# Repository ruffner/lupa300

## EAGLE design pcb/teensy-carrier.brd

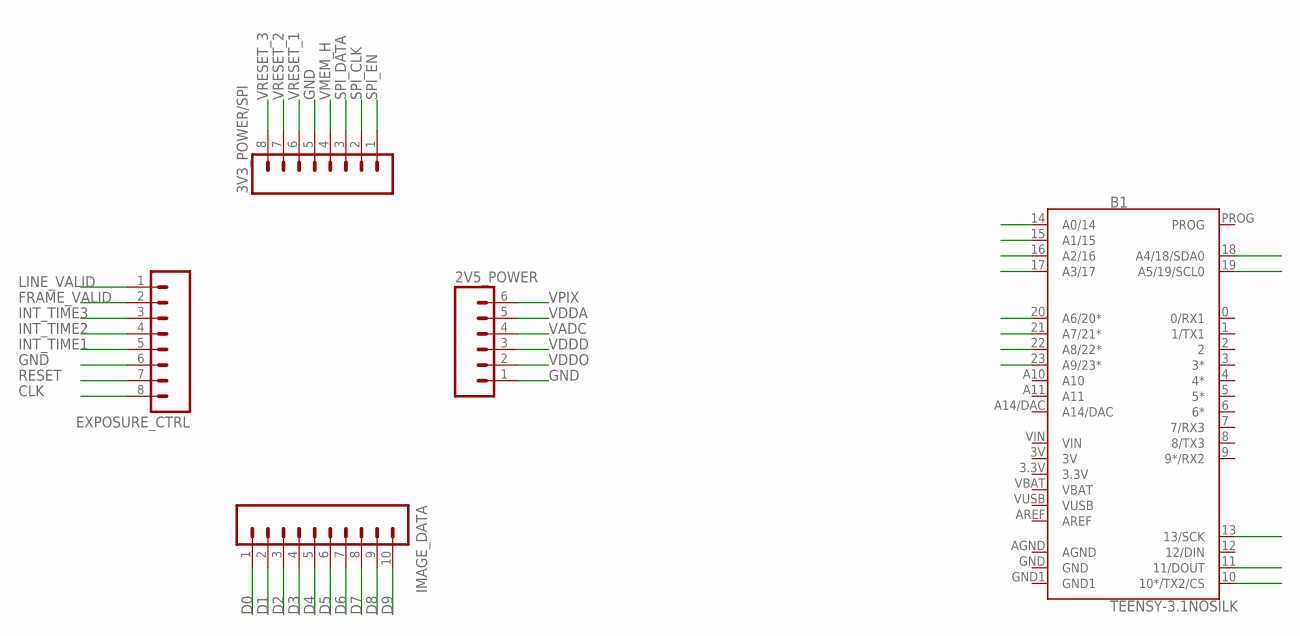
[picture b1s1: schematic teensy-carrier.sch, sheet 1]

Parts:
2V5_POWER: M06SILK_FEMALE_PTH; 1X06
3V3_POWER/SPI: M08; 1X08_ROUND
B1: TEENSY-3.1NOSILK; TEENSY-3.1_NOSILK
EXPOSURE_CTRL: M08; 1X08_ROUND
IMAGE_DATA: M10SILK_FEMALE_PTH; 1X10

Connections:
3.3V: B1.3.3V
3V: B1.3V
AGND: B1.AGND
CLK: EXPOSURE_CTRL.8
D0: B1.23 (A9/23*), IMAGE_DATA.1
D1: B1.22 (A8/22*), IMAGE_DATA.2
D2: B1.21 (A7/21*), IMAGE_DATA.3
D3: B1.20 (A6/20*), IMAGE_DATA.4
D4: B1.19 (A5/19/SCL0), IMAGE_DATA.5
D5: B1.18 (A4/18/SDA0), IMAGE_DATA.6
D6: B1.17 (A3/17), IMAGE_DATA.7
D7: B1.16 (A2/16), IMAGE_DATA.8
D8: B1.15 (A1/15), IMAGE_DATA.9
D9: B1.14 (A0/14), IMAGE_DATA.10
FRAME_VALID: EXPOSURE_CTRL.2
GND: 2V5_POWER.1, 3V3_POWER/SPI.5, B1.GND, EXPOSURE_CTRL.6; also elsewhere on the board
GND1: B1.GND1
INT_TIME1: EXPOSURE_CTRL.5
INT_TIME2: EXPOSURE_CTRL.4
INT_TIME3: EXPOSURE_CTRL.3
LINE_VALID: EXPOSURE_CTRL.1
RESET: EXPOSURE_CTRL.7
SPI_CLK: 3V3_POWER/SPI.2, B1.13 (13/SCK)
SPI_DATA: 3V3_POWER/SPI.3, B1.11 (11/DOUT)
SPI_EN: 3V3_POWER/SPI.1, B1.10 (10*/TX2/CS)
VADC: 2V5_POWER.4; also elsewhere on the board
VBAT: B1.VBAT
VDDA: 2V5_POWER.5; also elsewhere on the board
VDDD: 2V5_POWER.3; also elsewhere on the board
VDDO: 2V5_POWER.2; also elsewhere on the board
VIN: B1.VIN; also elsewhere on the board
VMEM_H: 3V3_POWER/SPI.4; also elsewhere on the board
VPIX: 2V5_POWER.6; also elsewhere on the board
VRESET_1: 3V3_POWER/SPI.6; also elsewhere on the board
VRESET_2: 3V3_POWER/SPI.7
VRESET_3: 3V3_POWER/SPI.8
VUSB: B1.VUSB

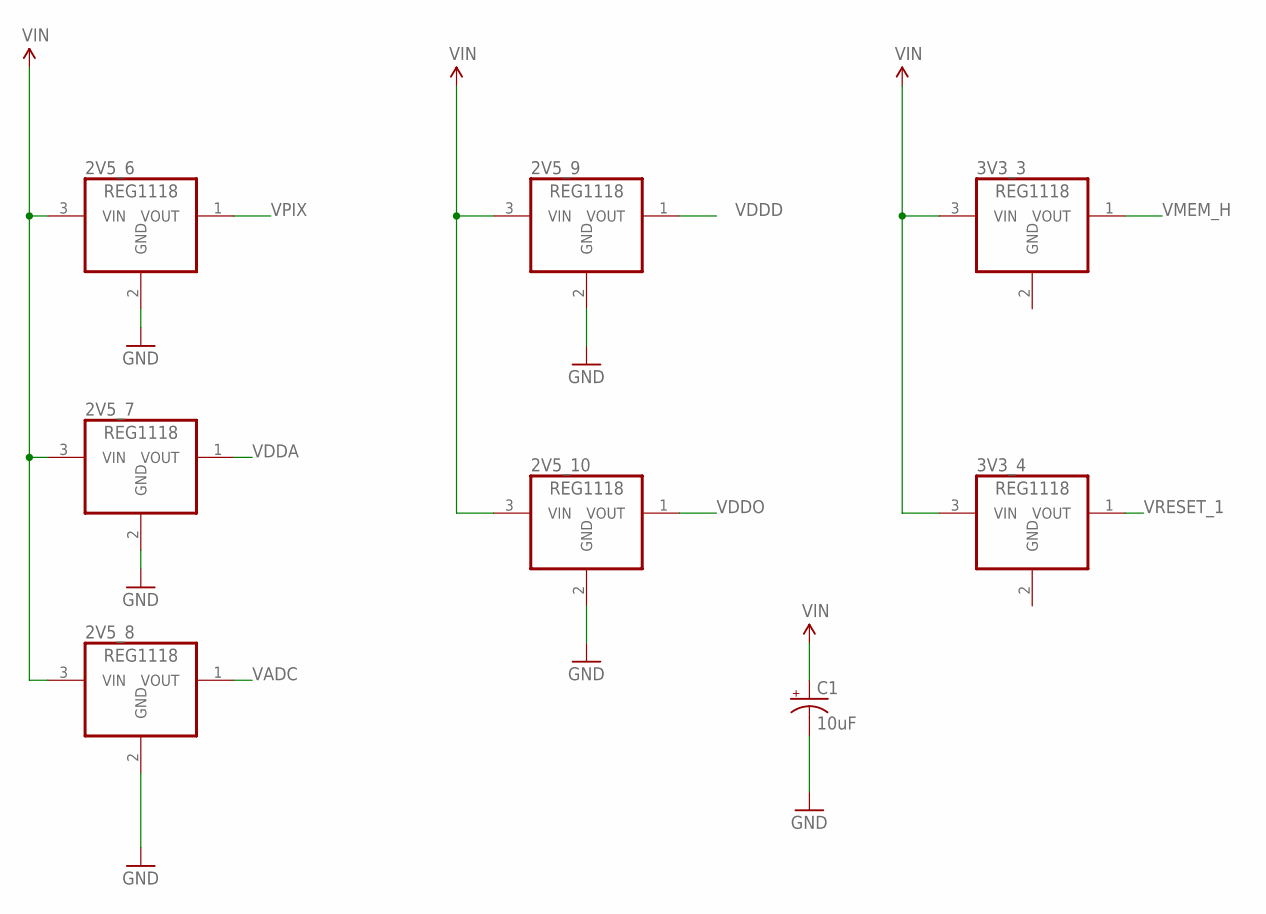
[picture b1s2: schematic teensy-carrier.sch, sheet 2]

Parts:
2V5_6, 2V5_7, 2V5_8, 2V5_9, 2V5_10, 3V3_3, 3V3_4: REG1118; SOT223
C1: 10uF; EIA3216

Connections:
GND: 2V5_6.2 (GND), 2V5_7.2 (GND), 2V5_8.2 (GND), 2V5_9.2 (GND), 2V5_10.2 (GND), 3V3_3.2 (GND), 3V3_4.2 (GND), C1.-; also elsewhere on the board
VADC: 2V5_8.1 (VOUT); also elsewhere on the board
VDDA: 2V5_7.1 (VOUT); also elsewhere on the board
VDDD: 2V5_9.1 (VOUT); also elsewhere on the board
VDDO: 2V5_10.1 (VOUT); also elsewhere on the board
VIN: 2V5_6.3 (VIN), 2V5_7.3 (VIN), 2V5_8.3 (VIN), 2V5_9.3 (VIN), 2V5_10.3 (VIN), 3V3_3.3 (VIN), 3V3_4.3 (VIN), C1.+; also elsewhere on the board
VMEM_H: 3V3_3.1 (VOUT); also elsewhere on the board
VPIX: 2V5_6.1 (VOUT); also elsewhere on the board
VRESET_1: 3V3_4.1 (VOUT); also elsewhere on the board

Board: 2 copper layers, 13 parts (8 on the bottom side), 22 nets, no tracks yet.

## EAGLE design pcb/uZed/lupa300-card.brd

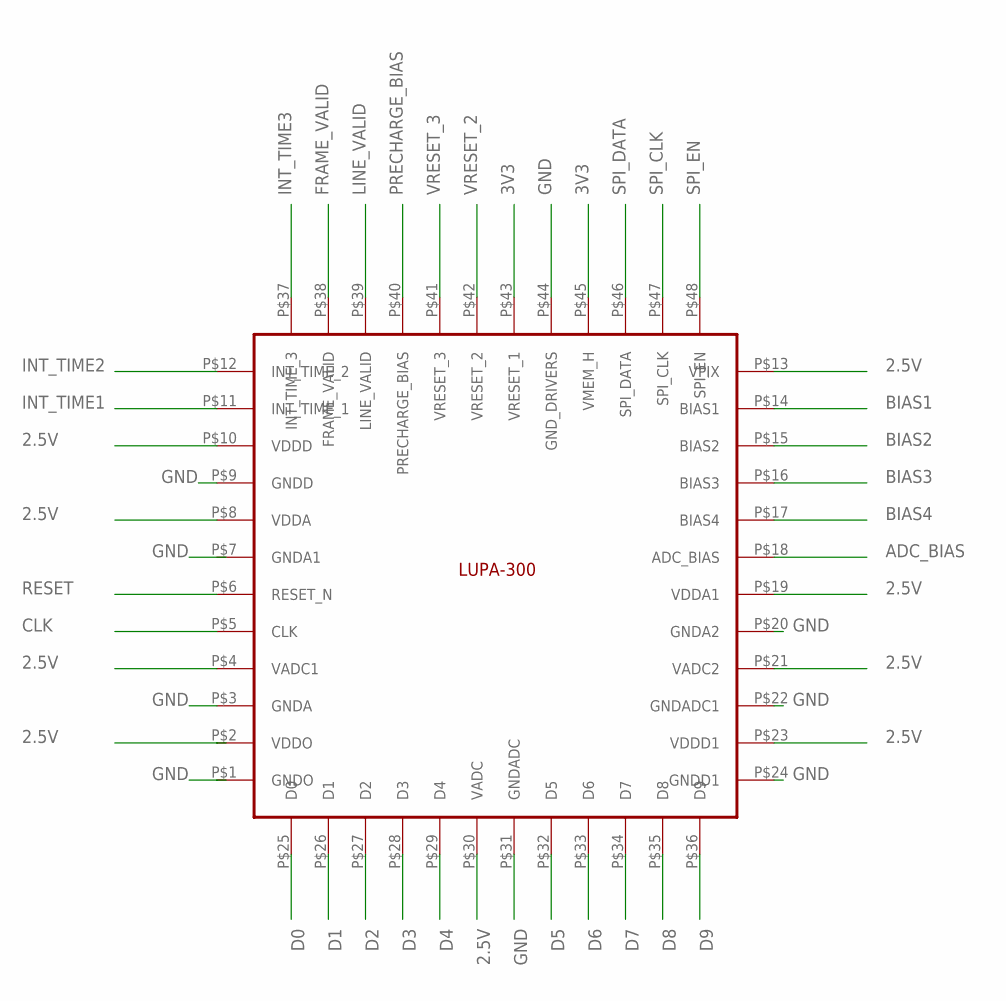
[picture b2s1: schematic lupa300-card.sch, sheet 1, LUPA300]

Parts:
U$1: LUPA300

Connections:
2.5V: U$1.P$2 (VDDO), U$1.P$4 (VADC1), U$1.P$8 (VDDA), U$1.P$10 (VDDD), U$1.P$13 (VPIX), U$1.P$19 (VDDA1), U$1.P$21 (VADC2), U$1.P$23 (VDDD1), U$1.P$30 (VADC); also elsewhere on the board
3V3: U$1.P$43 (VRESET_1), U$1.P$45 (VMEM_H); also elsewhere on the board
ADC_BIAS: U$1.P$18 (ADC_BIAS); also elsewhere on the board
BIAS1: U$1.P$14 (BIAS1); also elsewhere on the board
BIAS2: U$1.P$15 (BIAS2); also elsewhere on the board
BIAS3: U$1.P$16 (BIAS3); also elsewhere on the board
BIAS4: U$1.P$17 (BIAS4); also elsewhere on the board
CLK: U$1.P$5 (CLK); also elsewhere on the board
D0: U$1.P$25 (D0); also elsewhere on the board
D1: U$1.P$26 (D1); also elsewhere on the board
D2: U$1.P$27 (D2); also elsewhere on the board
D3: U$1.P$28 (D3); also elsewhere on the board
D4: U$1.P$29 (D4); also elsewhere on the board
D5: U$1.P$32 (D5); also elsewhere on the board
D6: U$1.P$33 (D6); also elsewhere on the board
D7: U$1.P$34 (D7); also elsewhere on the board
D8: U$1.P$35 (D8); also elsewhere on the board
D9: U$1.P$36 (D9); also elsewhere on the board
FRAME_VALID: U$1.P$38 (FRAME_VALID); also elsewhere on the board
GND: U$1.P$1 (GNDO), U$1.P$3 (GNDA), U$1.P$9 (GNDD), U$1.P$20 (GNDA2), U$1.P$22 (GNDADC1), U$1.P$24 (GNDD1), U$1.P$31 (GNDADC), U$1.P$44 (GND_DRIVERS); also elsewhere on the board
INT_TIME1: U$1.P$11 (INT_TIME_1); also elsewhere on the board
INT_TIME2: U$1.P$12 (INT_TIME_2); also elsewhere on the board
INT_TIME3: U$1.P$37 (INT_TIME_3); also elsewhere on the board
LINE_VALID: U$1.P$39 (LINE_VALID); also elsewhere on the board
PRECHARGE_BIAS: U$1.P$40 (PRECHARGE_BIAS); also elsewhere on the board
RESET: U$1.P$6 (RESET_N); also elsewhere on the board
SPI_CLK: U$1.P$47 (SPI_CLK); also elsewhere on the board
SPI_DATA: U$1.P$46 (SPI_DATA); also elsewhere on the board
SPI_EN: U$1.P$48 (SPI_EN); also elsewhere on the board
VRESET_2: U$1.P$42 (VRESET_2)
VRESET_3: U$1.P$41 (VRESET_3)

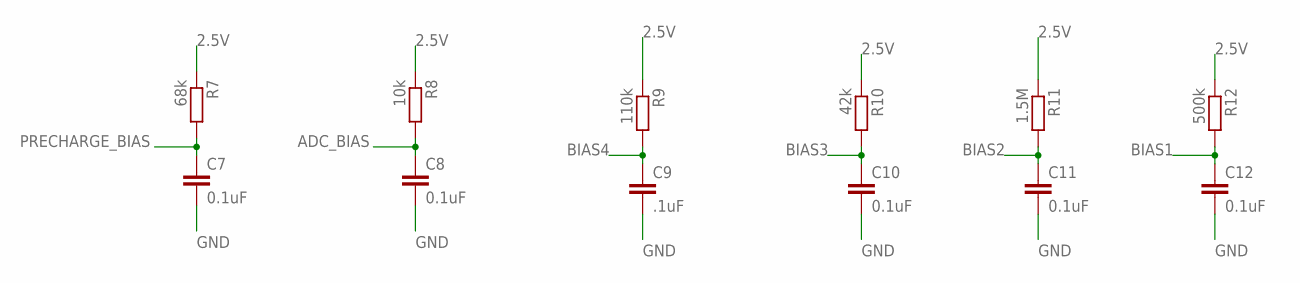
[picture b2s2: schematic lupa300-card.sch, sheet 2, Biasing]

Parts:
C7, C8, C10, C11, C12: 0.1uF; C0603K
C9: .1uF; C0603K
R7: 68k; R0603
R8: 10k; R0603
R9: 110k; R0603
R10: 42k; R0603
R11: 1.5M; R0603
R12: 500k; R0603

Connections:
2.5V: R7.1, R8.1, R9.1, R10.1, R11.1, R12.1; also elsewhere on the board
ADC_BIAS: C8.1, R8.2; also elsewhere on the board
BIAS1: C12.1, R12.2; also elsewhere on the board
BIAS2: C11.1, R11.2; also elsewhere on the board
BIAS3: C10.1, R10.2; also elsewhere on the board
BIAS4: C9.1, R9.2; also elsewhere on the board
GND: C7.2, C8.2, C9.2, C10.2, C11.2, C12.2; also elsewhere on the board
PRECHARGE_BIAS: C7.1, R7.2; also elsewhere on the board

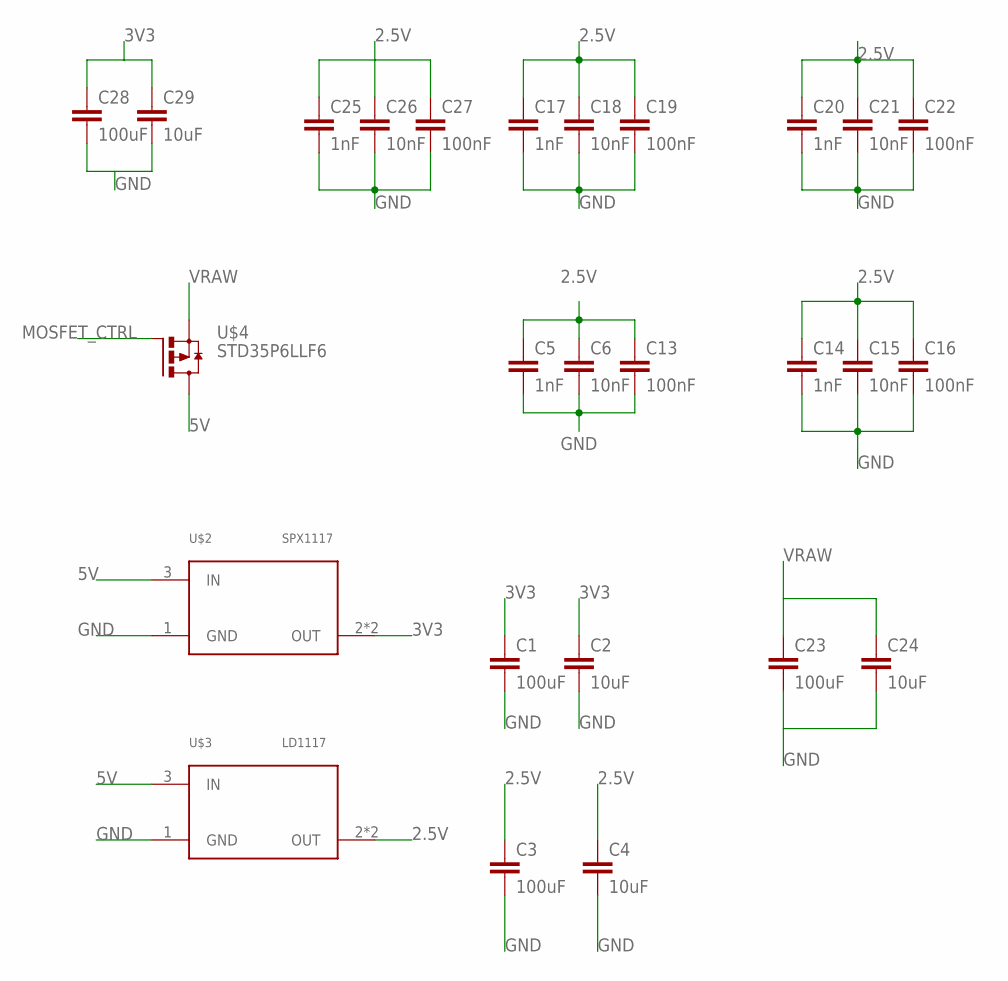
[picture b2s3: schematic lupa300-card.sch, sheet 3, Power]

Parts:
C1, C3: 100uF; C1206K
C2, C4: 10uF; C1206K
C5, C14, C17, C20, C25: 1nF; C0603
C6, C15, C18, C21, C26: 10nF; C0603
C13, C16, C19, C22, C27: 100nF; C0603
C23: 100uF; C1206
C24: 10uF; C1206
C28: 100uF; C0603
C29: 10uF; C0603
U$2: SPX1117; SOT223
U$3: LD1117; SOT223
U$4: STD35P6LLF6; DPACK

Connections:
2.5V: C3.1, C4.1, C5.1, C6.1, C13.1, C14.1, C15.1, C16.1, C17.1, C18.1, C19.1, C20.1, C21.1, C22.1, C25.1, C26.1, C27.1, U$3.2 (OUT), U$3.4 (OUT); also elsewhere on the board
3V3: C1.1, C2.1, C28.1, C29.1, U$2.2 (OUT), U$2.4 (OUT); also elsewhere on the board
5V: U$2.3 (IN), U$3.3 (IN), U$4.2 (D)
GND: C1.2, C2.2, C3.2, C4.2, C5.2, C6.2, C13.2, C14.2, C15.2, C16.2, C17.2, C18.2, C19.2, C20.2, C21.2, C22.2, C23.2, C24.2, C25.2, C26.2, C27.2, C28.2, C29.2, U$2.1 (GND), U$3.1 (GND); also elsewhere on the board
MOSFET_CTRL: U$4.1 (G); also elsewhere on the board
VRAW: C23.1, C24.1, U$4.3 (S); also elsewhere on the board

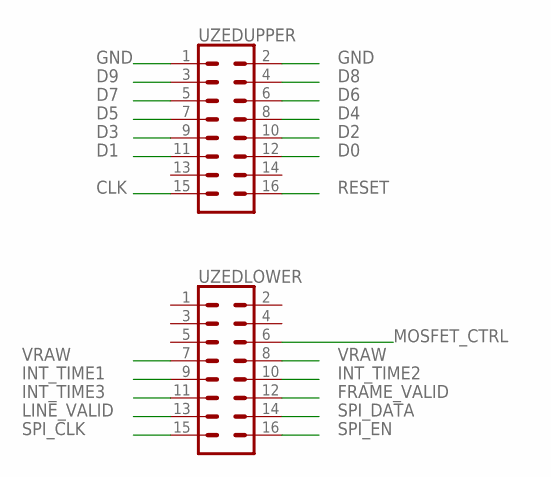
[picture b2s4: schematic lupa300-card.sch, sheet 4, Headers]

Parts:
UZEDLOWER: CONN_08X2; 2X8
UZEDUPPER: CONN_08X2; 2X8

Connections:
CLK: UZEDUPPER.15; also elsewhere on the board
D0: UZEDUPPER.12; also elsewhere on the board
D1: UZEDUPPER.11; also elsewhere on the board
D2: UZEDUPPER.10; also elsewhere on the board
D3: UZEDUPPER.9; also elsewhere on the board
D4: UZEDUPPER.8; also elsewhere on the board
D5: UZEDUPPER.7; also elsewhere on the board
D6: UZEDUPPER.6; also elsewhere on the board
D7: UZEDUPPER.5; also elsewhere on the board
D8: UZEDUPPER.4; also elsewhere on the board
D9: UZEDUPPER.3; also elsewhere on the board
FRAME_VALID: UZEDLOWER.12; also elsewhere on the board
GND: UZEDUPPER.1, UZEDUPPER.2; also elsewhere on the board
INT_TIME1: UZEDLOWER.9; also elsewhere on the board
INT_TIME2: UZEDLOWER.10; also elsewhere on the board
INT_TIME3: UZEDLOWER.11; also elsewhere on the board
LINE_VALID: UZEDLOWER.13; also elsewhere on the board
MOSFET_CTRL: UZEDLOWER.6; also elsewhere on the board
RESET: UZEDUPPER.16; also elsewhere on the board
SPI_CLK: UZEDLOWER.15; also elsewhere on the board
SPI_DATA: UZEDLOWER.14; also elsewhere on the board
SPI_EN: UZEDLOWER.16; also elsewhere on the board
VRAW: UZEDLOWER.7, UZEDLOWER.8; also elsewhere on the board

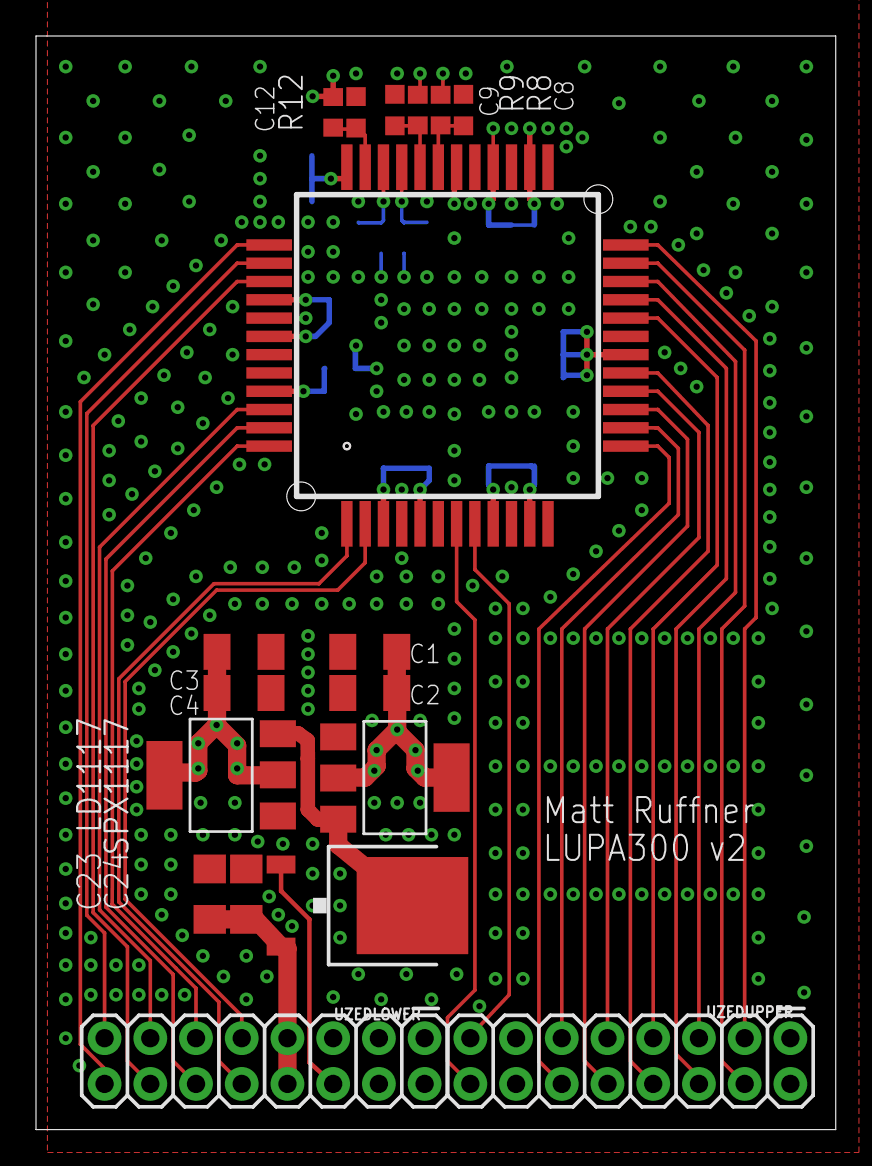
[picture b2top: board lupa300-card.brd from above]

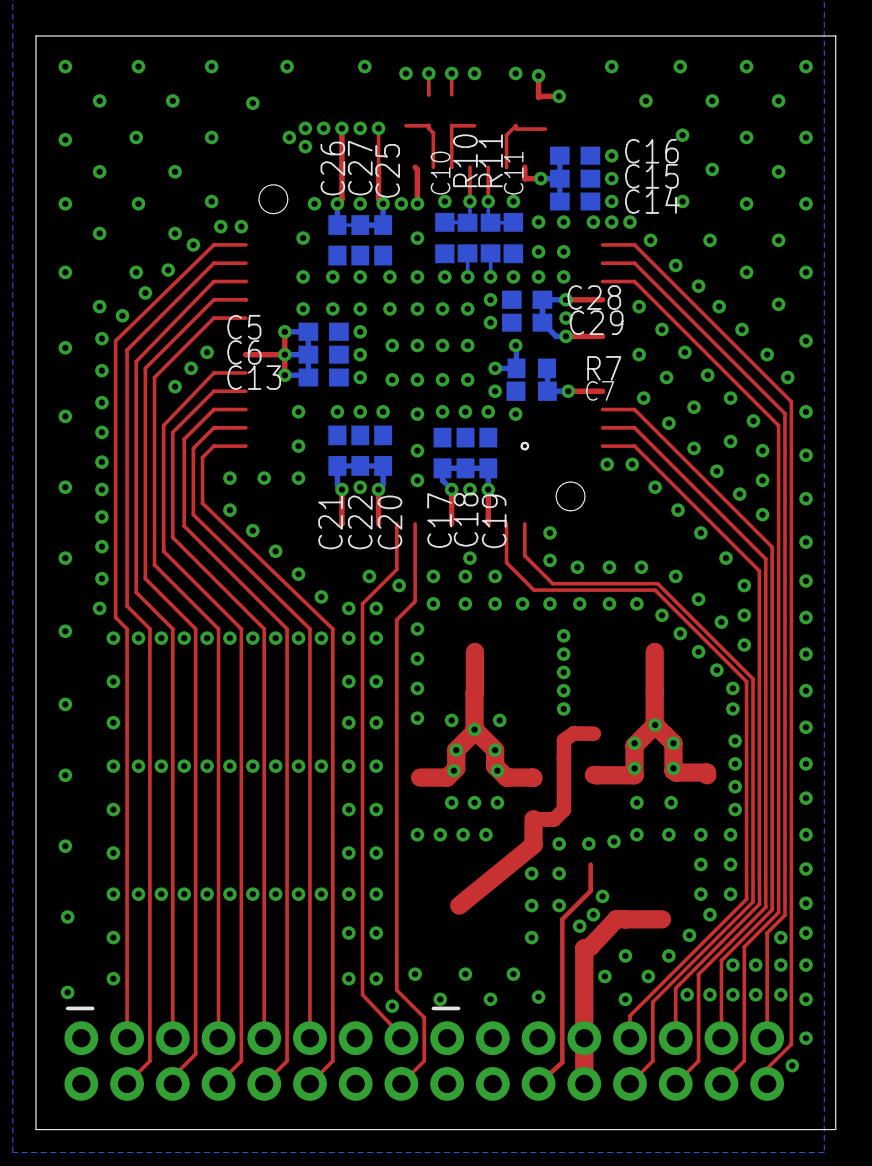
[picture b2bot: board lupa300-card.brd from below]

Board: 4 copper layers, 44.4 x 60.8 mm, 41 parts (23 on the bottom side), 32 nets.

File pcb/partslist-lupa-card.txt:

Partlist

Exported from lupa300-card.sch at 2/19/2018 2:41 PM

EAGLE Version 8.6.1 Copyright (c) 1988-2018 Autodesk, Inc.

Assembly variant: 

Part      Value          Device      Package  Library             Sheet

C1        100uF          C-EUC1206K  C1206K   rcl                 3
C2        10uF           C-EUC1206K  C1206K   rcl                 3
C3        100uF          C-EUC1206K  C1206K   rcl                 3
C4        10uF           C-EUC1206K  C1206K   rcl                 3
C5        1nF            C-EUC0603   C0603    rcl                 3
C6        10nF           C-EUC0603   C0603    rcl                 3
C7        0.1uF          C-EUC0603K  C0603K   rcl                 2
C8        0.1uF          C-EUC0603K  C0603K   rcl                 2
C9        .1uF           C-EUC0603K  C0603K   rcl                 2
C10       0.1uF          C-EUC0603K  C0603K   rcl                 2
C11       0.1uF          C-EUC0603K  C0603K   rcl                 2
C12       0.1uF          C-EUC0603K  C0603K   rcl                 2
C13       100nF          C-EUC0603   C0603    rcl                 3
C14       1nF            C-EUC0603   C0603    rcl                 3
C15       10nF           C-EUC0603   C0603    rcl                 3
C16       100nF          C-EUC0603   C0603    rcl                 3
C17       1nF            C-EUC0603   C0603    rcl                 3
C18       10nF           C-EUC0603   C0603    rcl                 3
C19       100nF          C-EUC0603   C0603    rcl                 3
C20       1nF            C-EUC0603   C0603    rcl                 3
C21       10nF           C-EUC0603   C0603    rcl                 3
C22       100nF          C-EUC0603   C0603    rcl                 3
C23       100uF          C-EUC1206   C1206    rcl                 3
C24       10uF           C-EUC1206   C1206    rcl                 3
C25       1nF            C-EUC0603   C0603    rcl                 3
C26       10nF           C-EUC0603   C0603    rcl                 3
C27       100nF          C-EUC0603   C0603    rcl                 3
C28       100uF          C-EUC0603   C0603    rcl                 3
C29       10uF           C-EUC0603   C0603    rcl                 3
R7        68k            R-EU_R0603  R0603    rcl                 2
R8        10k            R-EU_R0603  R0603    rcl                 2
R9        110k           R-EU_R0603  R0603    rcl                 2
R10       42k            R-EU_R0603  R0603    rcl                 2
R11       1.5M           R-EU_R0603  R0603    rcl                 2
R12       500k           R-EU_R0603  R0603    rcl                 2
U$1                      LUPA300     LUPA300  andon               1
U$2       SPX1117        SPX1117     SOT223   lupa300-components  3
U$3       LD1117         LD1117      SOT223   lupa300-components  3
U$4       STD35P6LLF6    STD35P6LLF6 DPACK    lupa300-components  3
UZEDLOWER                CONN_08X2   2X8      SparkFun-Connectors 4
UZEDUPPER                CONN_08X2   2X8      SparkFun-Connectors 4

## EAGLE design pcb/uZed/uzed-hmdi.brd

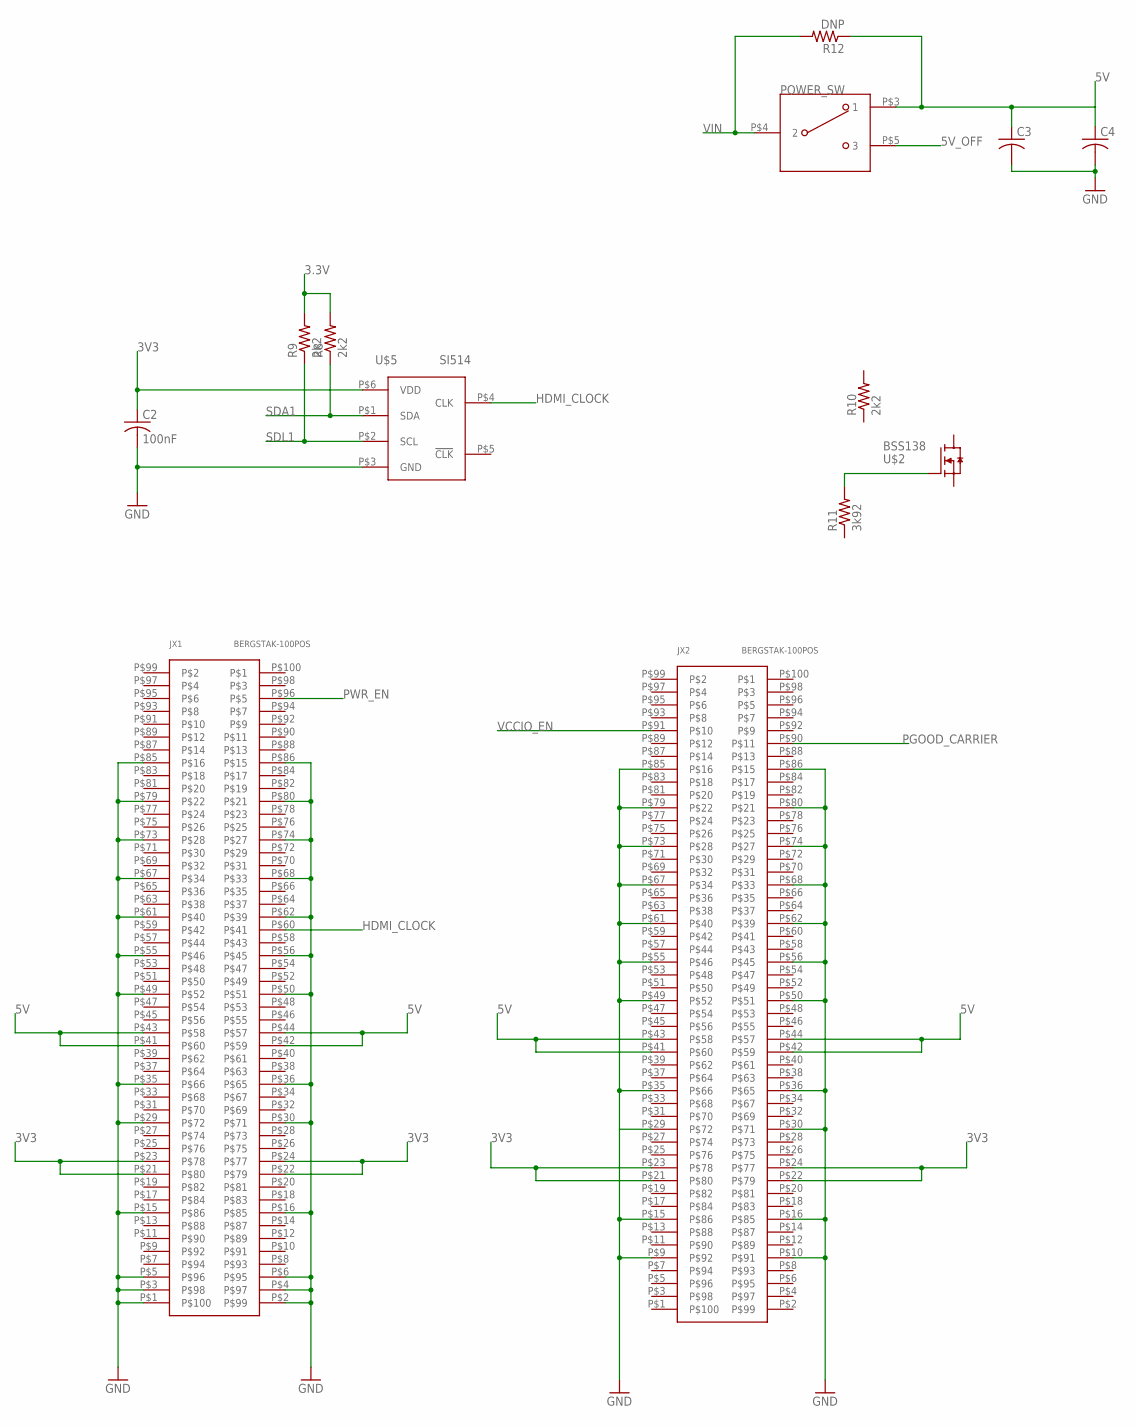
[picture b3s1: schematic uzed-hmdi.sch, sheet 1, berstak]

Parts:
C2: 100nF; C0603
C3: C-USC0603; C0603
C4: C-USC1206K; C1206K
JX1, JX2: BERGSTAK-100POS; BERG100POS
POWER_SW: T511006; SPDT
R8, R9, R10: 2k2; R0603
R11: 3k92; R0603
R12: DNP; R0603
U$2: BSS138; SOT23
U$5: SI514; XTAL-6PIN

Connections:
3.3V: R8.2, R9.2
3V3: C2.1, JX1.P$21, JX1.P$22, JX1.P$23, JX1.P$24, JX2.P$21, JX2.P$22, JX2.P$23, JX2.P$24, U$5.P$6 (VDD); also elsewhere on the board
5V: C3.1, C4.1, JX1.P$41, JX1.P$42, JX1.P$43, JX1.P$44, JX2.P$41, JX2.P$42, JX2.P$43, JX2.P$44, POWER_SW.P$3 (1), R12.1; also elsewhere on the board
5V_OFF: POWER_SW.P$5 (3)
GND: C2.2, C3.2, C4.2, JX1.P$1, JX1.P$2, JX1.P$3, JX1.P$4, JX1.P$5, JX1.P$6, JX1.P$15, JX1.P$16, JX1.P$29, JX1.P$30, JX1.P$35, JX1.P$36, JX1.P$49, JX1.P$50, JX1.P$55, JX1.P$56, JX1.P$61, JX1.P$62, JX1.P$67, JX1.P$68, JX1.P$73, JX1.P$74, JX1.P$79, JX1.P$80, JX1.P$85, JX1.P$86, JX2.P$9, JX2.P$10, JX2.P$15, JX2.P$16, JX2.P$29, JX2.P$30, JX2.P$35, JX2.P$36, JX2.P$49, JX2.P$50, JX2.P$55, JX2.P$56, JX2.P$61, JX2.P$62, JX2.P$67, JX2.P$68, JX2.P$73, JX2.P$74, JX2.P$79, JX2.P$80, JX2.P$85, JX2.P$86, U$5.P$3 (GND); also elsewhere on the board
HDMI_CLOCK: JX1.P$60, U$5.P$4 (CLK)
unnamed: R11.2, U$2.1 (G)
PGOOD_CARRIER: JX2.P$90
PWR_EN: JX1.P$96
SDA1: R8.1, U$5.P$1 (SDA)
SDL1: R9.1, U$5.P$2 (SCL)
VCCIO_EN: JX2.P$91
VIN: POWER_SW.P$4 (2), R12.2

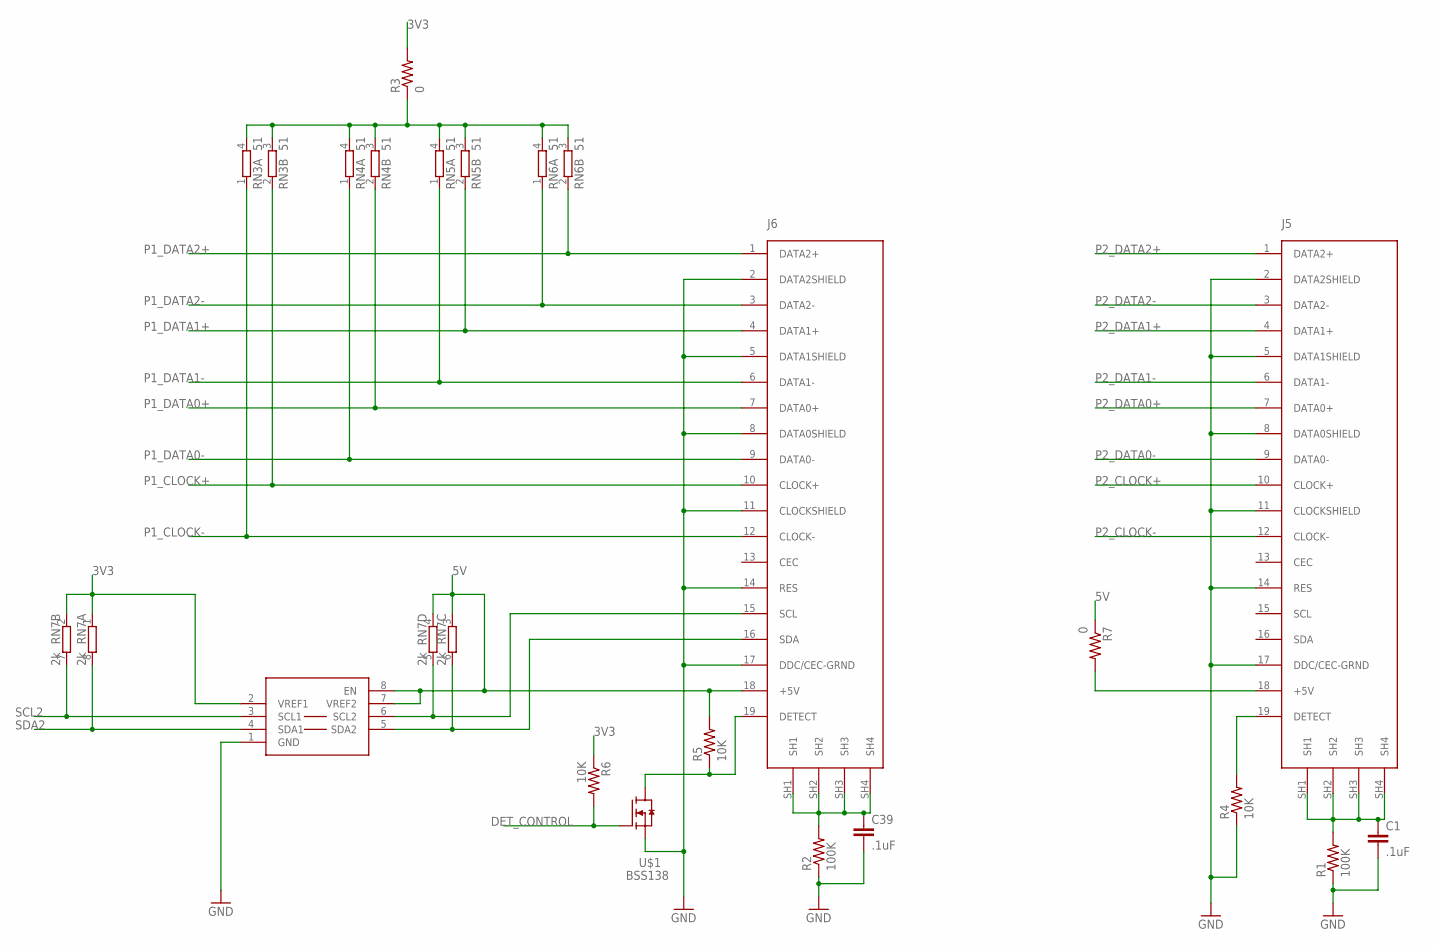
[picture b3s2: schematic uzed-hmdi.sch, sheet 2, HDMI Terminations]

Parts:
C1, C39: .1uF; C0603K
J5, J6: HDMI-TYPE-A-RECEPTICALFCI10029449; FCI-HDMI-TYPE-A-RECEPT
PCA9306: PCA9306; PSOP-8
R1, R2: 100K; R0603
R3, R7: 0; R0603
R4, R5, R6: 10K; R0603
RN3, RN4, RN5, RN6: 51; EXB34V
RN7: 2k; 0603-ARV
U$1: BSS138; SOT23

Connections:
3V3: PCA9306.2 (VREF1), R3.2, R6.1, RN7.1, RN7.2 (1); also elsewhere on the board
5V: J6.18 (+5V), PCA9306.7 (VREF2), PCA9306.8 (EN), R5.2, R7.1, RN7.3 (1), RN7.4 (1); also elsewhere on the board
DET_CONTROL: R6.2, U$1.1 (G)
GND: C1.2, C39.2, J5.2 (DATA2SHIELD), J5.5 (DATA1SHIELD), J5.8 (DATA0SHIELD), J5.11 (CLOCKSHIELD), J5.14 (RES), J5.17 (DDC/CEC-GRND), J6.2 (DATA2SHIELD), J6.5 (DATA1SHIELD), J6.8 (DATA0SHIELD), J6.11 (CLOCKSHIELD), J6.14 (RES), J6.17 (DDC/CEC-GRND), PCA9306.1 (GND), R1.1, R2.1, R4.1, U$1.2 (S); also elsewhere on the board
unnamed: C1.1, J5.SH1, J5.SH2, J5.SH3, J5.SH4, R1.2
unnamed: J5.19 (DETECT), R4.2
unnamed: R3.1, RN3.3 (2), RN3.4 (2), RN4.3 (2), RN4.4 (2), RN5.3 (2), RN5.4 (2), RN6.3 (2), RN6.4 (2)
unnamed: J6.19 (DETECT), R5.1, U$1.3 (D)
unnamed: J5.18 (+5V), R7.2
unnamed: J6.16 (SDA), PCA9306.5 (SDA2), RN7.6 (2)
unnamed: J6.15 (SCL), PCA9306.6 (SCL2), RN7.5 (2)
unnamed: C39.1, J6.SH1, J6.SH2, J6.SH3, J6.SH4, R2.2
P1_CLOCK+: J6.10 (CLOCK+), RN3.2 (1)
P1_CLOCK-: J6.12 (CLOCK-), RN3.1
P1_DATA0+: J6.7 (DATA0+), RN4.2 (1)
P1_DATA0-: J6.9 (DATA0-), RN4.1
P1_DATA1+: J6.4 (DATA1+), RN5.2 (1)
P1_DATA1-: J6.6 (DATA1-), RN5.1
P1_DATA2+: J6.1 (DATA2+), RN6.2 (1)
P1_DATA2-: J6.3 (DATA2-), RN6.1
P2_CLOCK+: J5.10 (CLOCK+)
P2_CLOCK-: J5.12 (CLOCK-)
P2_DATA0+: J5.7 (DATA0+)
P2_DATA0-: J5.9 (DATA0-)
P2_DATA1+: J5.4 (DATA1+)
P2_DATA1-: J5.6 (DATA1-)
P2_DATA2+: J5.1 (DATA2+)
P2_DATA2-: J5.3 (DATA2-)
SCL2: PCA9306.3 (SCL1), RN7.7 (2)
SDA2: PCA9306.4 (SDA1), RN7.8 (2)

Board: 2 copper layers, 31 parts (2 on the bottom side), 28 nets, no tracks yet.

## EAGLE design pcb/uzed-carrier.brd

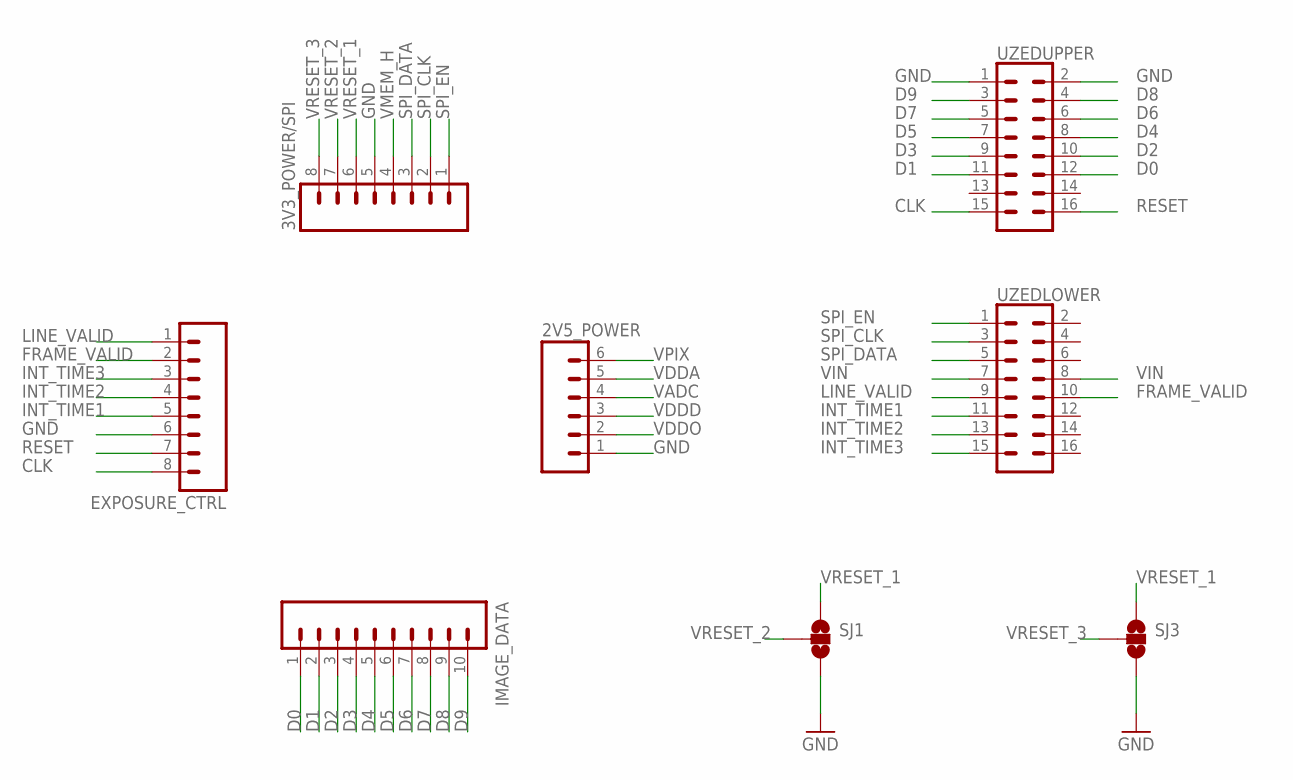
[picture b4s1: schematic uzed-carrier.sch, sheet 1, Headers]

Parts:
2V5_POWER: M06SILK_FEMALE_PTH; 1X06
3V3_POWER/SPI: M08; 1X08_ROUND
EXPOSURE_CTRL: M08; 1X08_ROUND
IMAGE_DATA: M10SILK_FEMALE_PTH; 1X10
SJ1, SJ3: SOLDERJUMPER_2WAYS; SJ_3
UZEDLOWER: CONN_08X2; 2X8
UZEDUPPER: CONN_08X2; 2X8

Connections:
CLK: EXPOSURE_CTRL.8, UZEDUPPER.15
D0: IMAGE_DATA.1, UZEDUPPER.12
D1: IMAGE_DATA.2, UZEDUPPER.11
D2: IMAGE_DATA.3, UZEDUPPER.10
D3: IMAGE_DATA.4, UZEDUPPER.9
D4: IMAGE_DATA.5, UZEDUPPER.8
D5: IMAGE_DATA.6, UZEDUPPER.7
D6: IMAGE_DATA.7, UZEDUPPER.6
D7: IMAGE_DATA.8, UZEDUPPER.5
D8: IMAGE_DATA.9, UZEDUPPER.4
D9: IMAGE_DATA.10, UZEDUPPER.3
FRAME_VALID: EXPOSURE_CTRL.2, UZEDLOWER.10
GND: 2V5_POWER.1, 3V3_POWER/SPI.5, EXPOSURE_CTRL.6, SJ1.3, SJ3.3, UZEDUPPER.1, UZEDUPPER.2; also elsewhere on the board
INT_TIME1: EXPOSURE_CTRL.5, UZEDLOWER.11
INT_TIME2: EXPOSURE_CTRL.4, UZEDLOWER.13
INT_TIME3: EXPOSURE_CTRL.3, UZEDLOWER.15
LINE_VALID: EXPOSURE_CTRL.1, UZEDLOWER.9
RESET: EXPOSURE_CTRL.7, UZEDUPPER.16
SPI_CLK: 3V3_POWER/SPI.2, UZEDLOWER.3
SPI_DATA: 3V3_POWER/SPI.3, UZEDLOWER.5
SPI_EN: 3V3_POWER/SPI.1, UZEDLOWER.1
VADC: 2V5_POWER.4; also elsewhere on the board
VDDA: 2V5_POWER.5; also elsewhere on the board
VDDD: 2V5_POWER.3; also elsewhere on the board
VDDO: 2V5_POWER.2; also elsewhere on the board
VIN: UZEDLOWER.7, UZEDLOWER.8; also elsewhere on the board
VMEM_H: 3V3_POWER/SPI.4; also elsewhere on the board
VPIX: 2V5_POWER.6; also elsewhere on the board
VRESET_1: 3V3_POWER/SPI.6, SJ1.1, SJ3.1; also elsewhere on the board
VRESET_2: 3V3_POWER/SPI.7, SJ1.2
VRESET_3: 3V3_POWER/SPI.8, SJ3.2

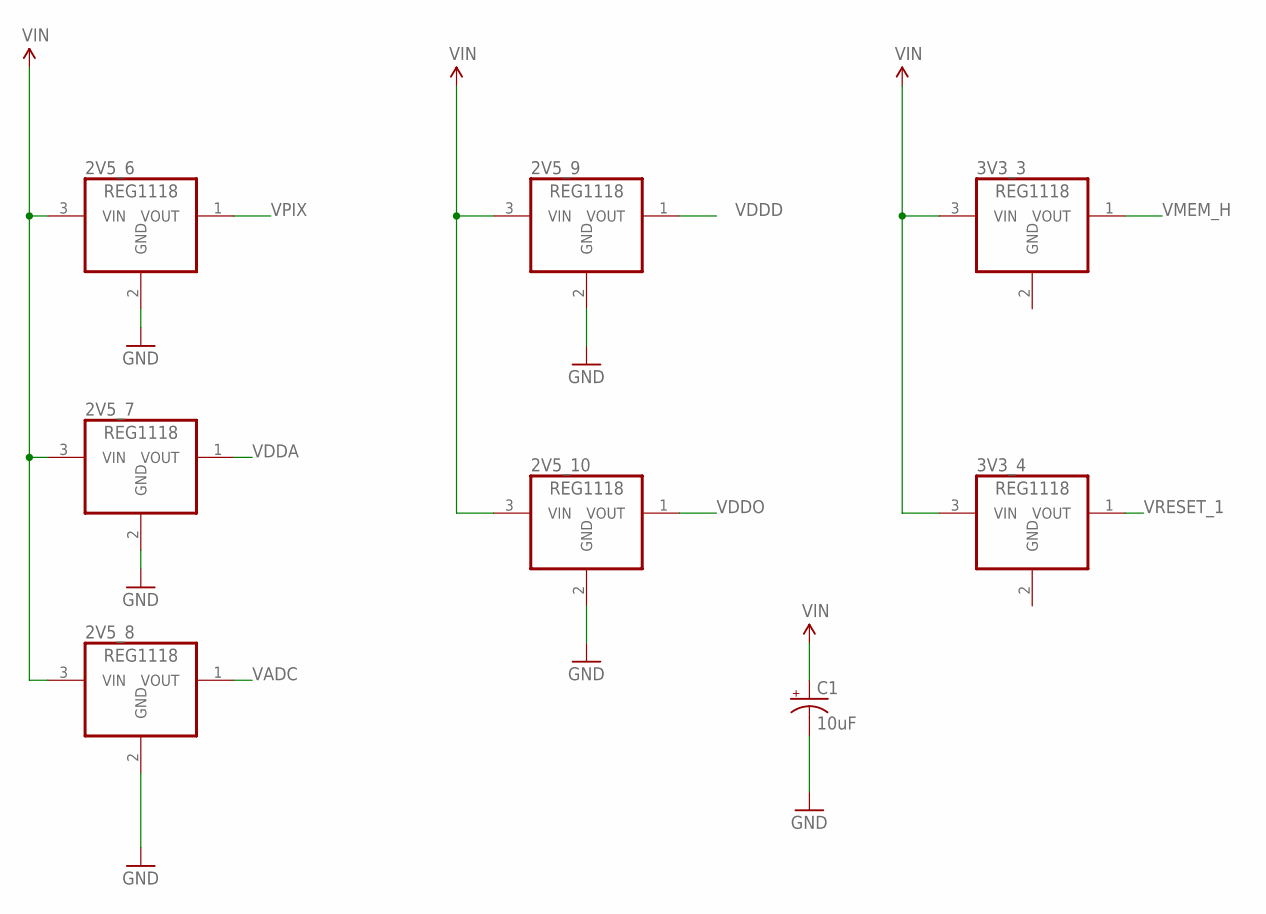
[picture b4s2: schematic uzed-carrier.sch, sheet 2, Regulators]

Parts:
2V5_6, 2V5_7, 2V5_8, 2V5_9, 2V5_10, 3V3_3, 3V3_4: REG1118; SOT223
C1: 10uF; EIA3216

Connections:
GND: 2V5_6.2 (GND), 2V5_7.2 (GND), 2V5_8.2 (GND), 2V5_9.2 (GND), 2V5_10.2 (GND), 3V3_3.2 (GND), 3V3_4.2 (GND), C1.-; also elsewhere on the board
VADC: 2V5_8.1 (VOUT); also elsewhere on the board
VDDA: 2V5_7.1 (VOUT); also elsewhere on the board
VDDD: 2V5_9.1 (VOUT); also elsewhere on the board
VDDO: 2V5_10.1 (VOUT); also elsewhere on the board
VIN: 2V5_6.3 (VIN), 2V5_7.3 (VIN), 2V5_8.3 (VIN), 2V5_9.3 (VIN), 2V5_10.3 (VIN), 3V3_3.3 (VIN), 3V3_4.3 (VIN), C1.+; also elsewhere on the board
VMEM_H: 3V3_3.1 (VOUT); also elsewhere on the board
VPIX: 2V5_6.1 (VOUT); also elsewhere on the board
VRESET_1: 3V3_4.1 (VOUT); also elsewhere on the board

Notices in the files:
parts and their libraries:
SparkFun-Connectors: Licensing: Creative Commons ShareAlike 4.0 International - https://creativecommons.org/licenses/by-sa/4.0
